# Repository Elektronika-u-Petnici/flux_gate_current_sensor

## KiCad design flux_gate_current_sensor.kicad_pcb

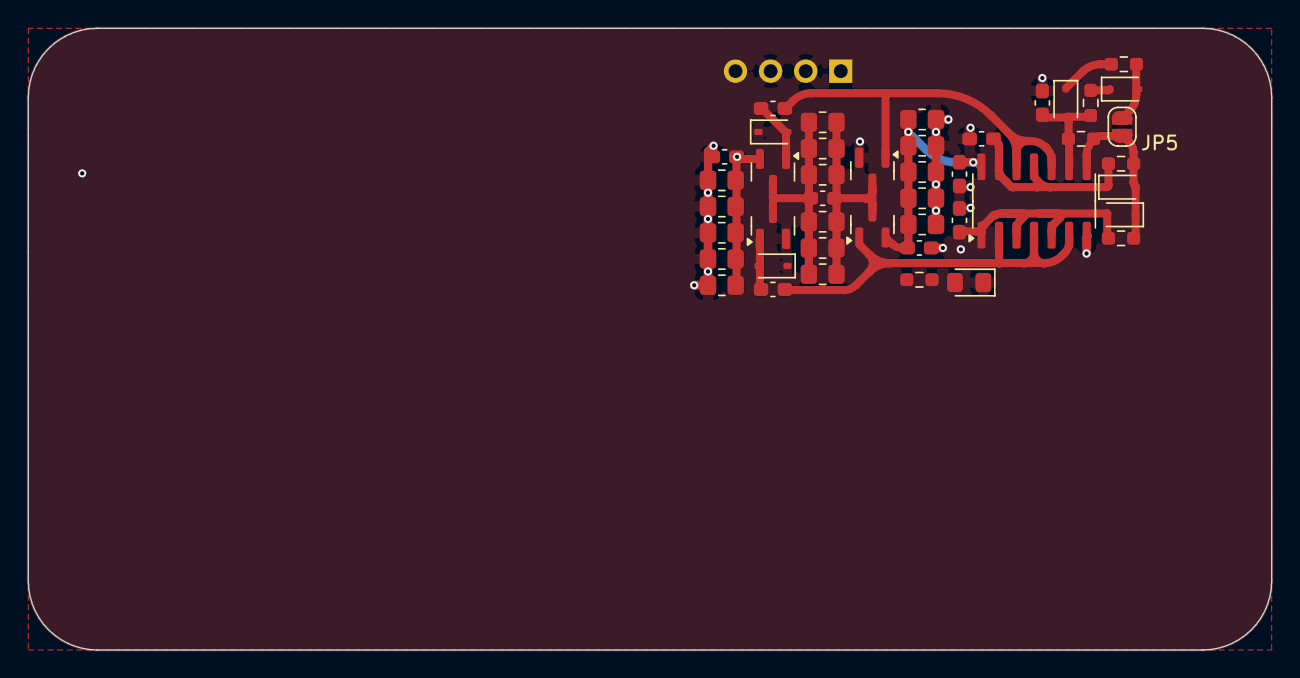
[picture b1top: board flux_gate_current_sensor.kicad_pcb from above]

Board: 2 copper layers, 90.0 x 45.0 mm, 45 parts (1 on the bottom side), 17 nets.

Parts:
C1, C2, C10, C41, C43, C49, C50, C51, C52, C53, C54, C55, C56, C57, C58, C65: 10u; R_0805_2012Metric_Pad1.20x1.40mm_HandSolder
C4, C31, C35, C42, C60: 100n; C_0603_1608Metric_Pad1.08x0.95mm_HandSolder
C5, C7: 100p; C_0603_1608Metric_Pad1.08x0.95mm_HandSolder
C17: 1n; C_0603_1608Metric_Pad1.08x0.95mm_HandSolder
C46: 1u; C_0603_1608Metric_Pad1.08x0.95mm_HandSolder
D3: GREEN_LED; LED_0805_2012Metric_Pad1.15x1.40mm_HandSolder
D8, D9, D10, D11, D12, D13: 1N4148WS; D_SOD-323
J1: Conn_01x04_Pin; PinHeader_1x04_P2.54mm_Vertical
JP5: Jumper_2_Open; SolderJumper-2_P1.3mm_Open_RoundedPad1.0x1.5mm
Q8, Q10: AO3401A; SOT-23
Q13, Q14: AO3400A; SOT-23
R1, R9: 1k; R_0603_1608Metric_Pad0.98x0.95mm_HandSolder
R37, R38: 100k; R_0603_1608Metric_Pad0.98x0.95mm_HandSolder
R40: 10k; R_0603_1608Metric_Pad0.98x0.95mm_HandSolder
R51: 20k; R_0603_1608Metric_Pad0.98x0.95mm_HandSolder
U7: 74HC14; SOIC-14_3.9x8.7mm_P1.27mm

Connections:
0: C1.1, C5.1, C7.1, C10.1, C17.1, C31.1, C35.1, C46.1, C51.1, C52.1, C53.1, C54.1, C55.1, C56.1, C57.1, C58.1, D3.1 (K), D8.1 (K), D13.1 (K), J1.2, J1.3, Q10.2 (S), Q13.2 (S), U7.7 (GND)
/Power supply/MID_DRV: C2.1, C41.1, C43.1, C49.1, C50.1, C60.2, C65.1, Q8.3 (D), Q13.3 (D)
/Power supply/MID_REC: C2.2, C41.2, C43.2, C49.2, C50.2, C60.1, C65.2, Q10.3 (D), Q14.3 (D)
CLK: D11.2 (A), D12.1 (K), JP5.1 (A), R9.2, R40.2, R51.1, U7.8
NMOS_GATE: C42.1, Q13.1 (G), U7.10, U7.12
unnamed: D3.2 (A), R1.1
unnamed: C4.2, D8.2 (A), Q10.1 (G)
unnamed: D9.2 (A), JP5.2 (B), R38.2
unnamed: D9.1 (K), R37.2
unnamed: C17.2, D10.2 (A), R37.1, R51.2, U7.9
unnamed: D10.1 (K), R38.1
unnamed: C5.2, D11.1 (K), R40.1, U7.11, U7.13
unnamed: C7.2, D12.2 (A), R9.1, U7.1, U7.3, U7.5
unnamed: C42.2, D13.2 (A), Q14.1 (G)
PMOS_GATE: C4.1, Q8.1 (G), U7.2, U7.4, U7.6
V_{cc}: C10.2, C31.2, C46.2, C55.2, C56.2, C57.2, C58.2, J1.1, Q8.2 (S), R1.2, U7.14 (VCC)
V_{ee}: C1.2, C35.2, C51.2, C52.2, C53.2, C54.2, J1.4, Q14.2 (S)
